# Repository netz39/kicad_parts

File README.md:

# KiCad Parts
Library parts missing in KiCad

Library of components missing in [KiCad](http://kicad-pcb.org//), and
some breakout boards which are almost like library parts, and some
datasheets for the previously mentioned parts …

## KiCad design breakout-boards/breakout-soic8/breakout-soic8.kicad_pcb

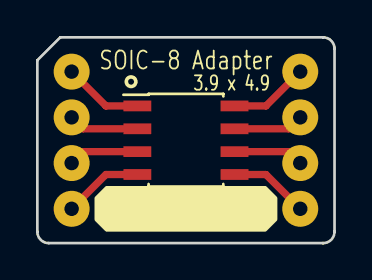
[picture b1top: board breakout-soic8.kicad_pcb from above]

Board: 2 copper layers, 16.5 x 11.4 mm, 9 parts (0 on the bottom side), 8 nets.

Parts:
P1: DIL8; SOIC-8_3.9x4.9mm_Pitch1.27mm
W1, W2, W3, W4, W5, W6, W7, W8: TEST_1P; SolderWirePad_single_0-8mmDrill

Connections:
unnamed: P1.1, W1.1
unnamed: P1.2, W2.1
unnamed: P1.3, W3.1
unnamed: P1.4, W4.1
unnamed: P1.5, W5.1
unnamed: P1.6, W6.1
unnamed: P1.7, W7.1
unnamed: P1.8, W8.1

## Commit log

2017-03-13 A more extensive description
2017-03-13 Switch Datasheets
2017-03-13 Initial lib with SRKL switch
2017-03-13 SRKL switch footprint with and w/o LED
2017-03-17 Add casing holes to SWITCH_SRKL
2017-03-18 Add casing holes to SWITCH_SRKL_LED
2017-04-25 Datasheet for Microchip 23A512/23LC512 SRAM
2017-04-25 Add schematic component for Microchip 23A512/23LC512 SRAM
2017-04-25 Add the (future) datasheet path on github
2017-05-01 CAT4101 data sheet
2017-05-01 CAT4101 schema component
2017-05-01 Panelized PCB
2017-05-01 SOIC-8 Adapter Kicad project
2017-05-01 SOIC-8 Adapter Single PCB
2017-05-01 SOIC-8 Adapter Schematic
2017-07-22 footprint for 16mm batteryholder kzh16-1
2017-12-09 Footprint for AKL 101-02
2017-12-09 Footprint for AKL 101-04
2017-12-09 Footprint for ALK 101-03
2018-03-11 Datasheet for VQE 7-segment displays
2018-03-11 Symbol for VQE24 7-segment display
2018-03-11 Footprint for VQE24 7-segment display
2018-03-11 Symbol for VQE23 7-segment display
2018-03-11 Symbol for VQE21 7-segment display
2018-03-11 Symbol for VQE22 7-segment display
2018-03-18 MCP9808: Datasheet
2018-03-18 MCP9808: Symbol
2018-03-18 Add Doclib file
2018-04-15 PCA 9551 datasheet
2018-04-15 Add part for PCA9551
2018-04-16 PCA9551: set VCC to passive
2018-04-16 WS2812: datasheet
2018-04-16 WS2812: part
2018-12-29 Molex HDD Power plug
2019-01-05 Corrected measurements based on real part
2019-01-06 Fix holes and clearance
2019-02-18 Documentation
2019-02-18 Pack Kicad gerber files for DirtyPCBs
2019-04-09 add VQB28 7-Segment and Dotmatrix symbols and footprints
2019-04-20 fix missing pin errors
